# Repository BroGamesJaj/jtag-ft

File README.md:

# JTAG-FT

A simple FT2232HP board to program and debug fpgas and other jtag capable hardware.

features:
- JTAG, 14pin xilinx jtag connector compatible
- UART
- Voltage level shifters for both UART and JTAG (1V1-5V)

setups:
- Xilinx fpga programmer:\
  download Vivado(2025.1 or newer) then use the included program_ftdi.\
  command:\
  ```program_ftdi -write -ftdi FT2232HP -serial 0ABC01 -vendor "my vendor co" -board "my board" -desc "my product desc" ```\
  After this Vivado should be able to see the board as a valid programming cable
  [official guide](https://docs.amd.com/r/en-US/ug908-vivado-programming-debugging/JTAG-Cables-and-Devices-Supported-by-hw_server)

- Lattice fpga programmer: TODO

- Altera fpga programmer: TODO

images:
assembled board

FT2232HP properties flashed

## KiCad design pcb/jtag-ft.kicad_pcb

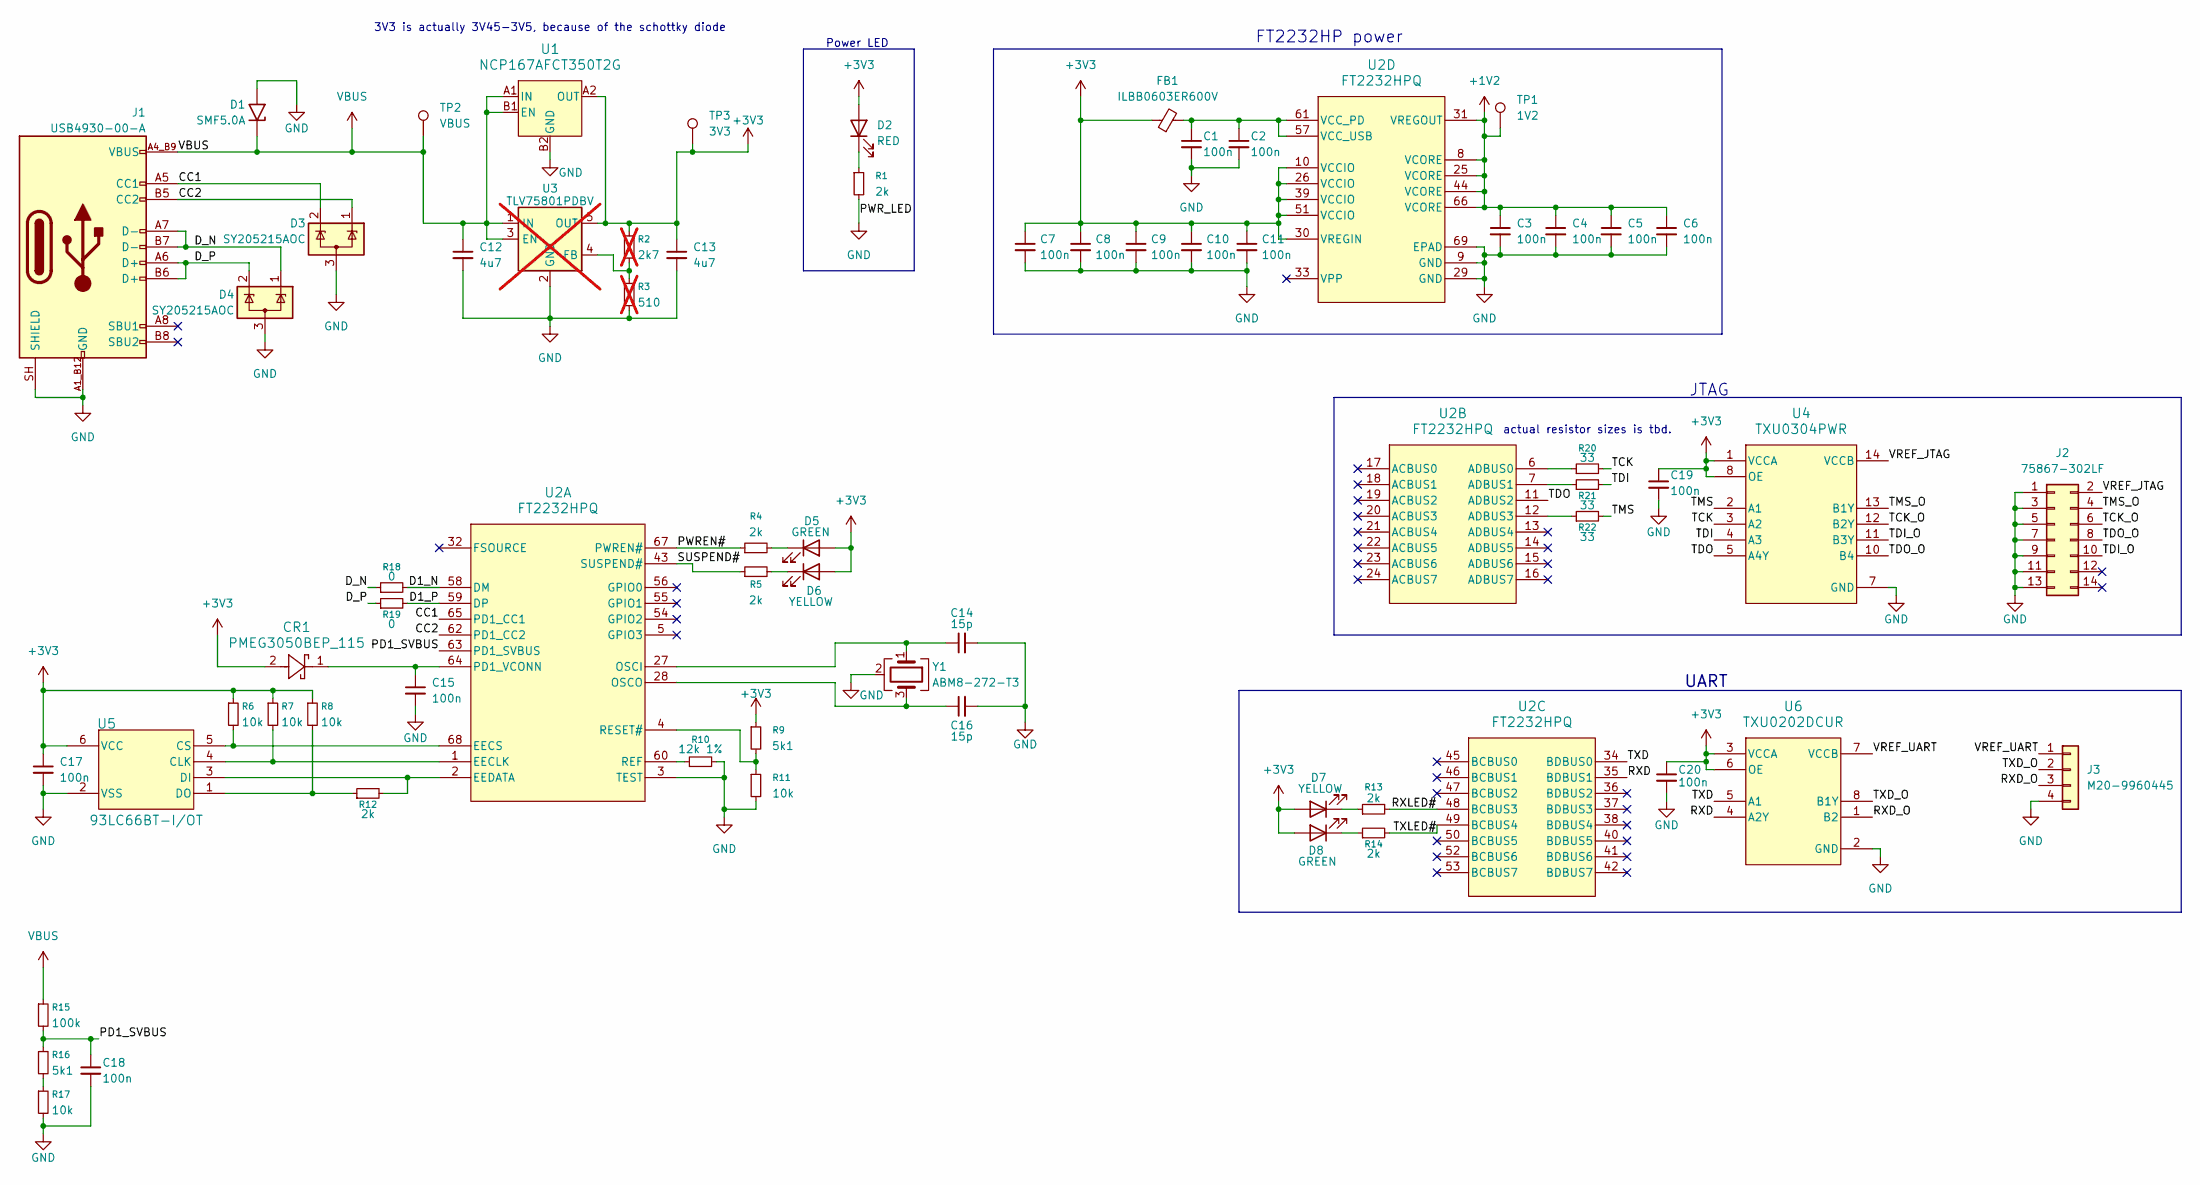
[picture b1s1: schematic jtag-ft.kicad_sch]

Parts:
C1, C2, C3, C4, C5, C6, C7, C8, C9, C10, C11, C15, C17, C18, C19, C20: 100n; C_0402_1005Metric_Pad0.74x0.62mm_HandSolder
C12, C13: 4u7; C_0603_1608Metric_Pad1.08x0.95mm_HandSolder
C14, C16: 15p; C_0603_1608Metric_Pad1.08x0.95mm_HandSolder
CR1: PMEG3050BEP_115; CFP5_SOD128_NEX
D1: SMF5.0A; D_SMF
D2: RED; LED_0603_1608Metric
D3, D4: SY205215AOC; SOT-23
D5, D8: GREEN; LED_0603_1608Metric
D6, D7: YELLOW; LED_0603_1608Metric
FB1: ILBB0603ER600V; R_0603_1608Metric_Pad0.98x0.95mm_HandSolder
J1: USB4930-00-A; GCT_USB4930-00-A_REVA
J2: 75867-302LF; IDC-Header_2x07_P2.54mm_Horizontal
J3: M20-9960445; PinHeader_1x04_P2.54mm_Horizontal
R1, R4, R5, R12, R13, R14: 2k; R_0603_1608Metric_Pad0.98x0.95mm_HandSolder
R2: 2k7; R_0402_1005Metric_Pad0.72x0.64mm_HandSolder; not fitted
R3: 510; R_0402_1005Metric_Pad0.72x0.64mm_HandSolder; not fitted
R6, R7, R8, R11, R17: 10k; R_0402_1005Metric_Pad0.72x0.64mm_HandSolder
R9, R16: 5k1; R_0603_1608Metric_Pad0.98x0.95mm_HandSolder
R10: 12k 1%; R_0402_1005Metric_Pad0.72x0.64mm_HandSolder
R15: 100k; R_0603_1608Metric_Pad0.98x0.95mm_HandSolder
R18, R19: 0; R_0402_1005Metric_Pad0.72x0.64mm_HandSolder
R20, R21, R22: 33; R_0402_1005Metric_Pad0.72x0.64mm_HandSolder
TP1: 1V2
TP2: VBUS
TP3: 3V3
U1: NCP167AFCT350T2G; WLCSP4_0P64X0P64_ONS
U2: FT2232HPQ; QFN68_FT2232_FTD
U3: TLV75801PDBV; SOT-23-5; not fitted
U4: TXU0304PWR; TSSOP14_PW_TEX
U5: 93LC66BT-I/OT; SOT-23-6_MC_MCH
U6: TXU0202DCUR; SO8_DCU_TEX
Y1: ABM8-272-T3; Crystal_SMD_Abracon_ABM8AIG-4Pin_3.2x2.5mm

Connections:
+1V2: C3.1, C4.1, C5.1, C6.1, TP1.1, U2.8 (VCORE), U2.25 (VCORE), U2.31 (VREGOUT), U2.44 (VCORE), U2.66 (VCORE)
+3V3: C7.1, C8.1, C9.1, C10.1, C11.1, C13.1, C17.1, C19.1, C20.1, CR1.2, D2.2 (A), D5.2 (A), D6.2 (A), D7.2 (A), D8.2 (A), FB1.1, R2.1, R6.1, R7.1, R8.1, R9.1, TP3.1, U1.A2 (OUT), U2.10 (VCCIO), U2.26 (VCCIO), U2.30 (VREGIN), U2.39 (VCCIO), U2.51 (VCCIO), U3.5 (OUT), U4.1 (VCCA), U4.8 (OE), U5.6 (VCC), U6.3 (VCCA), U6.6 (OE)
/CC1: D3.2 (K), J1.A5 (CC1), U2.65 (PD1_CC1)
/CC2: D3.1 (K), J1.B5 (CC2), U2.62 (PD1_CC2)
/D1_N: R18.2, U2.58 (DM)
/D1_P: R19.2, U2.59 (DP)
/D_N: D4.1 (K), J1.A7 (D-), J1.B7 (D-), R18.1
/D_P: D4.2 (K), J1.A6 (D+), J1.B6 (D+), R19.1
/PD1_SVBUS: C18.1, R15.2, R16.1, U2.63 (PD1_SVBUS)
/PWREN#: R4.1, U2.67 (PWREN#)
/RXD: U2.35 (BDBUS1), U6.4 (A2Y)
/RXD_O: J3.3, U6.1 (B2)
/RXLED#: R13.2, U2.48 (BCBUS3)
/SUSPEND#: R5.1, U2.43 (SUSPEND#)
/TCK: R20.2, U4.3 (A2)
/TCK_O: J2.6, U4.12 (B2Y)
/TDI: R21.2, U4.4 (A3)
/TDI_O: J2.10, U4.11 (B3Y)
/TDO: U2.11 (ADBUS2), U4.5 (A4Y)
/TDO_O: J2.8, U4.10 (B4)
/TMS: R22.2, U4.2 (A1)
/TMS_O: J2.4, U4.13 (B1Y)
/TXD: U2.34 (BDBUS0), U6.5 (A1)
/TXD_O: J3.2, U6.8 (B1Y)
/TXLED#: R14.2, U2.49 (BCBUS4)
/VREF_JTAG: J2.2, U4.14 (VCCB)
/VREF_UART: J3.1, U6.7 (VCCB)
GND: C1.2, C2.2, C3.2, C4.2, C5.2, C6.2, C7.2, C8.2, C9.2, C10.2, C11.2, C12.2, C13.2, C14.2, C15.2, C16.2, C17.2, C18.2, C19.2, C20.2, D1.2 (A2), D3.3 (A), D4.3 (A), J1.A1_B12 (GND), J1.B1_A12 (GND), J1.SH (SHIELD), J2.1, J2.3, J2.5, J2.7, J2.9, J2.11, J2.13, J3.4, R1.2, R3.2, R10.2, R11.2, R17.2, U1.B2 (GND), U2.3 (TEST), U2.9 (GND), U2.29 (GND), U2.69 (EPAD), U3.2 (GND), U4.6 (NC), U4.7 (GND), U4.9 (NC), U5.2 (VSS), U6.2 (GND), Y1.2 (G), Y1.4 (G)
unnamed: D2.1 (K), R1.1
unnamed: D5.1 (K), R4.2
unnamed: D6.1 (K), R5.2
unnamed: D7.1 (K), R13.1
unnamed: D8.1 (K), R14.1
unnamed: R16.2, R17.1
unnamed: R7.2, U2.1 (EECLK), U5.4 (CLK)
unnamed: R6.2, U2.68 (EECS), U5.5 (CS)
unnamed: R12.2, U2.2 (EEDATA), U5.3 (DI)
unnamed: C14.1, U2.27 (OSCI), Y1.1
unnamed: C16.1, U2.28 (OSCO), Y1.3
unnamed: C15.1, CR1.1, U2.64 (PD1_VCONN)
unnamed: R10.1, U2.60 (REF)
unnamed: R9.2, R11.1, U2.4 (RESET#)
unnamed: R20.1, U2.6 (ADBUS0)
unnamed: R21.1, U2.7 (ADBUS1)
unnamed: R22.1, U2.12 (ADBUS3)
unnamed: C1.1, C2.1, FB1.2, U2.57 (VCC_USB), U2.61 (VCC_PD)
unnamed: R2.2, R3.1, U3.4 (FB)
unnamed: R8.2, R12.1, U5.1 (DO)
VBUS: C12.1, D1.1 (A1), J1.A4_B9 (VBUS), J1.B4_A9 (VBUS), R15.1, TP2.1, U1.A1 (IN), U1.B1 (EN), U3.1 (IN), U3.3 (EN)

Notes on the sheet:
FT2232HP power
JTAG
actual resistor sizes is tbd.
3V3 is actually 3V45-3V5, because of the schottky diode
UART
Power LED

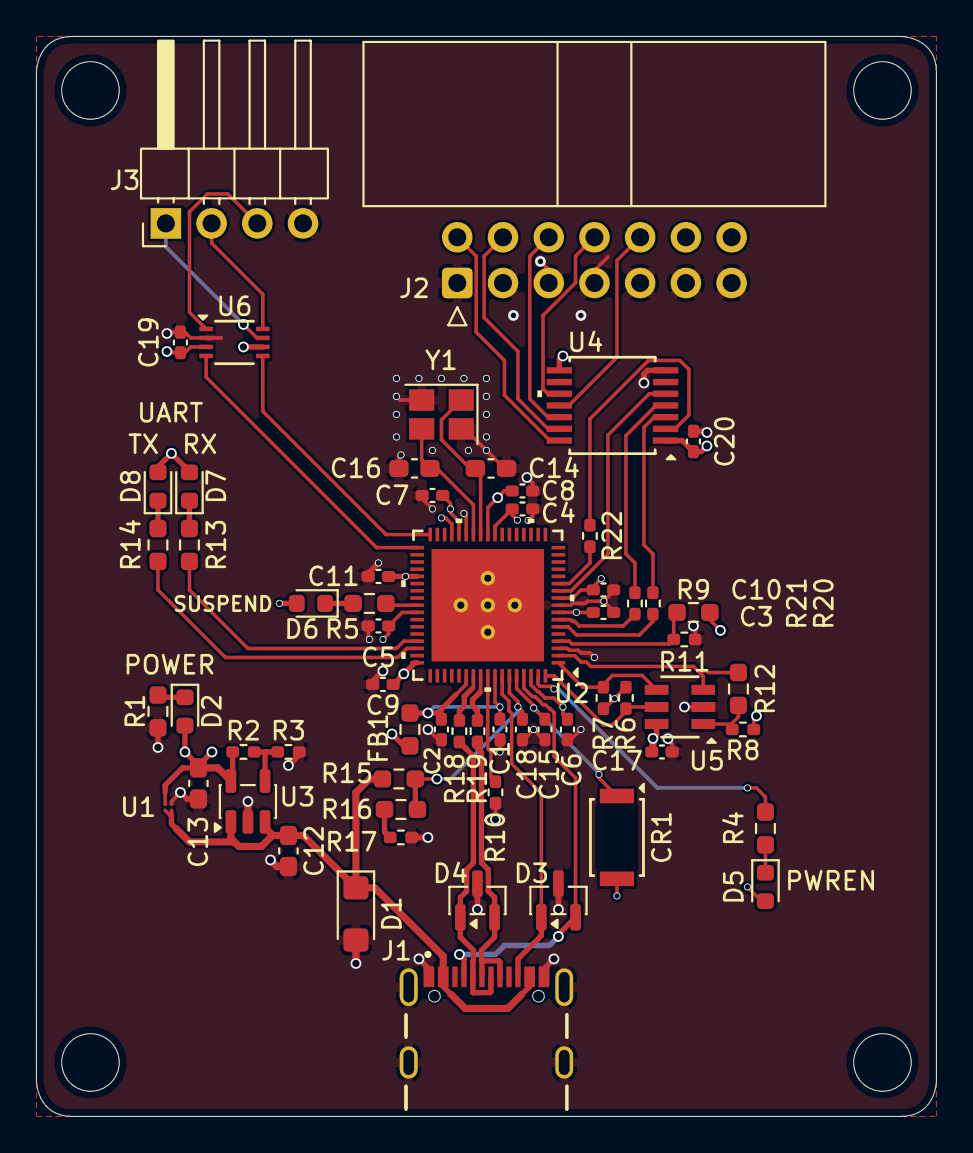
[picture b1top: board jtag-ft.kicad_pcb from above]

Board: 4 copper layers, 50.0 x 60.0 mm, 62 parts (0 on the bottom side), 49 nets.

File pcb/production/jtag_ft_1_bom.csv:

Designator,Footprint,Quantity,Value,LCSC Part #
"C1, C10, C11, C15, C17, C18, C19, C2, C20, C3, C4, C5, C6, C7, C8, C9",0402,16,100n,
"C12, C13",0603,2,4u7,
"C14, C16",0603,2,15p,
CR1,CFP5_SOD128_NEX,1,PMEG3050BEP_115,
D1,D_SMF,1,SMF5.0A,
D2,0603,1,RED,
"D3, D4",SOT-23,2,SY205215AOC,
"D5, D8",0603,2,GREEN,
"D6, D7",0603,2,YELLOW,
FB1,0603,1,ILBB0603ER600V,
J1,GCT_USB4930-00-A_REVA,1,USB4930-00-A,
J2,IDC-Header_2x07_P2.54mm_Horizontal,1,75867-302LF,
J3,PinHeader_1x04_P2.54mm_Horizontal,1,M20-9960445,
"R1, R12, R13, R14, R4, R5",0603,6,2k,
R10,0402,1,12k 1%,
"R11, R17, R6, R7, R8",0402,5,10k,
R15,0603,1,100k,
"R16, R9",0603,2,5k1,
"R18, R19",0402,2,0,
R2,0402,1,2k7,
"R20, R21, R22",0402,3,33,
R3,0402,1,510,
U1,WLCSP4_0P64X0P64_ONS,1,NCP167AFCT350T2G,
U2,QFN68_FT2232_FTD,1,FT2232HPQ,
U3,SOT-23-5,1,TLV75801PDBV,
U4,TSSOP14_PW_TEX,1,TXU0304PWR,
U5,SOT-23-6_MC_MCH,1,93LC66BT-I/OT,
U6,SO8_DCU_TEX,1,TXU0202DCUR,
Y1,Crystal_SMD_Abracon_ABM8AIG-4Pin_3.2x2.5mm,1,ABM8-272-T3,
